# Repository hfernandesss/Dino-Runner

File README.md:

# Dino-Runner
O projeto consiste em uma recriação do jogo "Dino Runner" do google em Arduino.

# O jogo - Menu Iniciar

# Placa PCB

# Caixinha

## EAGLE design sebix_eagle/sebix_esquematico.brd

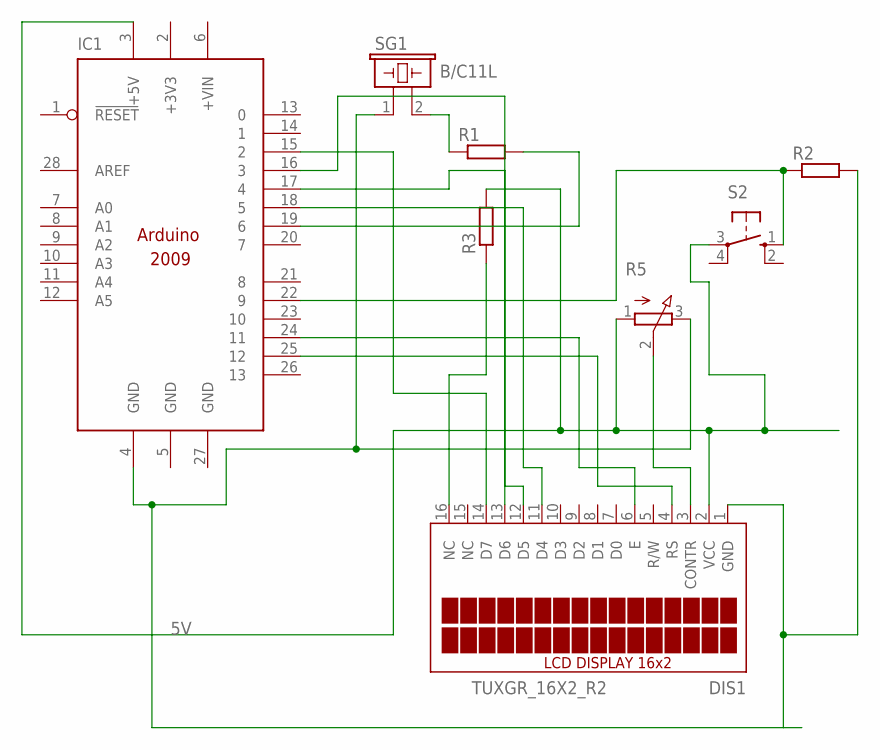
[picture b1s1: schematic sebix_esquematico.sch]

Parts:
DIS1: TUXGR_16X2_R2
IC1: ARDUINO2009_10; ARDUINO2009
R1, R2: R-EU_0207/10; 0207/10
R3: R-EU_0204/7; 0204/7
R5: 3RP/1610N
S2: 10-XX; B3F-10XX
SG1: B/C11L

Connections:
5V: DIS1.2 (VCC), IC1.3 (+5V), R3.2, R5.1 (A), S2.3
+3V3: IC1.2 (+3V3)
GND: IC1.5 (GND), IC1.27 (GND)
unnamed: DIS1.16 (NC), R3.1
unnamed: DIS1.3 (CONTR), R5.2 (S)
unnamed: R1.1, SG1.2
unnamed: DIS1.4 (RS), IC1.25 (12)
unnamed: DIS1.6 (E), IC1.24 (11)
unnamed: DIS1.11 (D4), IC1.18 (5)
unnamed: DIS1.12 (D5), IC1.17 (4)
unnamed: IC1.19 (6), R1.2
unnamed: DIS1.13 (D6), IC1.16 (3)
unnamed: DIS1.14 (D7), IC1.15 (2)
unnamed: IC1.22 (9), R2.1, S2.1 (S)
unnamed: DIS1.1 (GND), IC1.4 (GND), R2.2, R5.3 (E), SG1.1

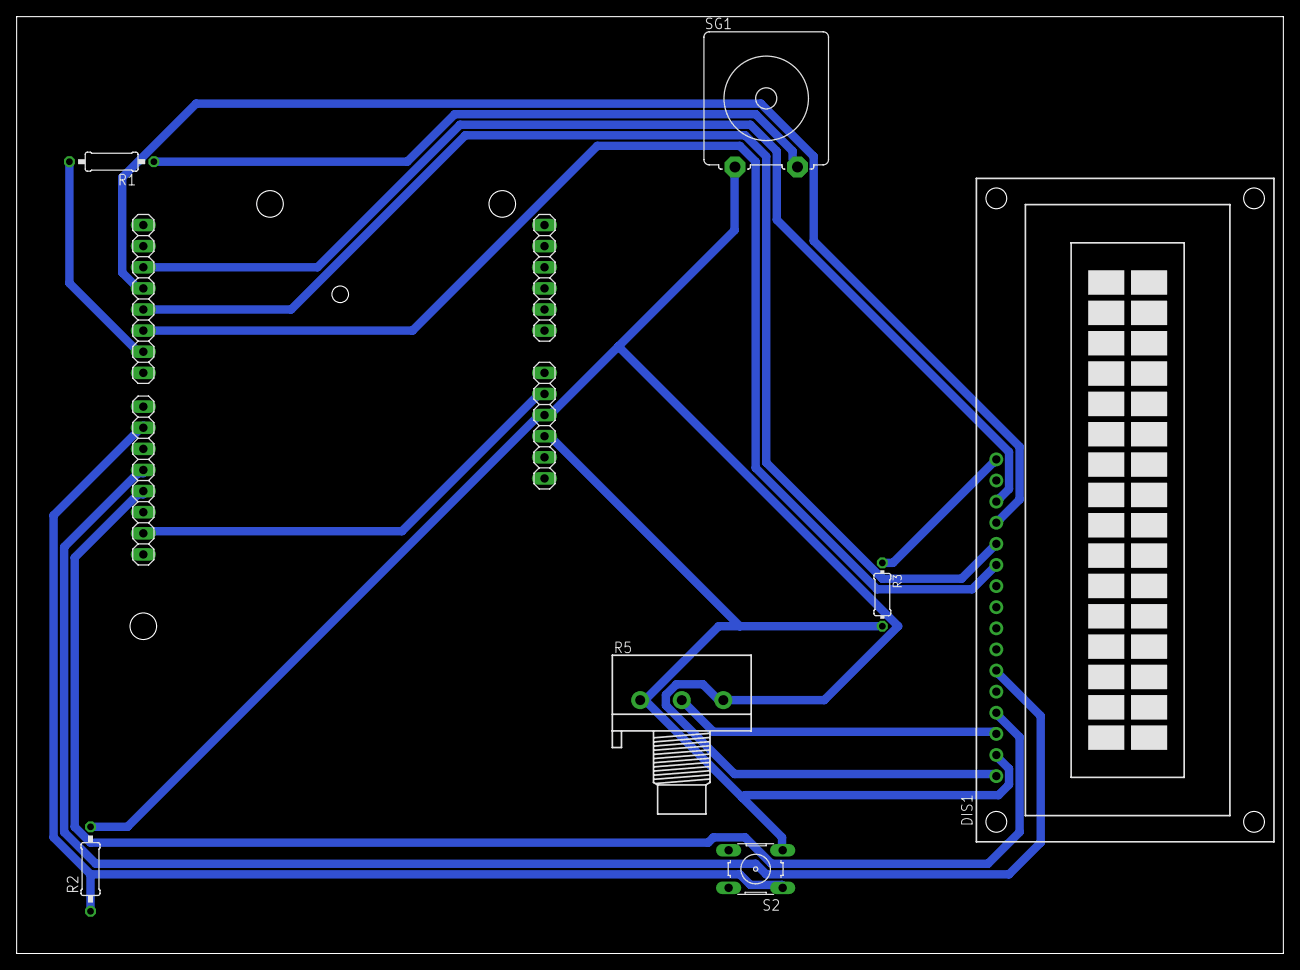
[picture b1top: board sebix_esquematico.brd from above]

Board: 2 copper layers, 152.4 x 112.7 mm, 8 parts (0 on the bottom side), 14 nets.

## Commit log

2021-04-24 Update dino_runner.ino
    Código comentado e finalizado
